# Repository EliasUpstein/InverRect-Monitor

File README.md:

# InverRect-Monitor

**Plataforma Ciberfísica de Simulación, Control HIL y Monitoreo SCADA para Electrónica de Potencia**

---

## 1. Visión y Propósito del Proyecto

**InverRect-Monitor** es una plataforma integral de ingeniería que fusiona la **simulación matemática de alta precisión** con el **control y monitoreo físico en tiempo real** de convertidores estáticos de potencia (rectificadores controlados y no controlados monofásicos y trifásicos, e inversores).

En el estudio y operación de la electrónica de potencia, existe a menudo una desconexión entre:
1. **Los modelos analíticos teóricos:** cálculo de potencias bajo condiciones no senoidales, descomposición en series de Fourier, impacto de armónicas en la red y comportamiento de cargas complejas ($R$, $L$, $C$).
2. **La implementación física de control:** detección precisa del cruce por cero de la red ($50\text{ Hz} / 60\text{ Hz}$), sincronización de microsegundos para el disparo de compuertas (SCR / TRIAC) y aislamiento galvánico de alta tensión.

**InverRect-Monitor** resuelve esta brecha creando un entorno tipo **Hardware-in-the-Loop (HIL) y SCADA**:
* Permite al usuario **analizar, simular y descomponer armónicamente** 12 topologías de convertidores bajo el estándar internacional **IEEE 1459**.
* Permite actuar como **consola SCADA de control remoto**, enviando el ángulo de disparo ($\alpha$) en tiempo real vía **Wi-Fi / UDP** hacia un microcontrolador **ESP32** dedicado al control físico de potencia, garantizando sincronismo estricto e inmunidad a retardos de software.

---

## 2. Arquitectura Global del Sistema Ciberfísico

El sistema opera mediante una división estricta entre la **estación de supervisión de alto nivel (PC)** y el **nodo de control de potencia en tiempo real (ESP32)**:

```
┌─────────────────────────────────────────────────────────────────────────────┐
│                      ESTACIÓN DE SUPERVISIÓN (PC)                           │
│                                                                             │
│   ┌─────────────────────┐   ┌────────────────────────┐   ┌──────────────┐   │
│   │     calculos.py     │◄─►│      interfaz.py       │◄─►│   main.py    │   │
│   │ (NumPy/IEEE 1459/SF)│   │(Tkinter/Matplotlib/UDP)│   │ (Controller) │   │
│   └─────────────────────┘   └───────────┬────────────┘   └──────────────┘   │
└─────────────────────────────────────────┼───────────────────────────────────┘
                                          │ Datagramas UDP ("ALFA:xx.x")
                                          │ Wi-Fi 802.11 (Puerto 8888)
                                          ▼
┌─────────────────────────────────────────────────────────────────────────────┐
│                   NODO DE CONTROL EN TIEMPO REAL (ESP32)                    │
│                                                                             │
│   ┌─────────────────────────────────────┐   ┌───────────────────────────┐   │
│   │               CORE 0                │   │          CORE 1           │   │
│   │   • Tarea FreeRTOS Comunicaciones   │   │   • ISR Cruce por Cero    │   │
│   │   • Servidor UDP & ArduinoOTA       │◄─►│   • Hardware Timer (1 MHz)│   │
│   │   • Sincronización atómica (MUX)    │   │   • Pulso de compuerta    │   │
│   └─────────────────────────────────────┘   └─────────────┬─────────────┘   │
└───────────────────────────────────────────────────────────┼─────────────────┘
                                                            │
                      ┌─────────────────────────────────────┴─────────────┐
                      ▼                                                   ▼
            ┌───────────────────┐                               ┌───────────────────┐
            │  ENTRADA DIGITAL  │                               │  SALIDA DIGITAL   │
            │  GPIO 18 (ZC)     │                               │  GPIO 19 (Gate)   │
            └─────────▲─────────┘                               └─────────┬─────────┘
                      │                                                   │
                      │ Pulso 50 Hz                                       │ Pulso 50 µs
            ┌─────────┴─────────┐                               ┌─────────┴─────────┐
            │ Optoacoplador ZC  │                               │ Driver Opto-TRIAC │
            │      (PC817)      │                               │     (MOC3021)     │
            └─────────▲─────────┘                               └─────────┬─────────┘
                      │                                                   │
     Red Eléctrica ───┴───────────────── Circuito de Potencia ────────────┴──► Carga
     (220V CA / 50 Hz)                   (Tiristores SCR / TRIAC)              (R-L-C)
```

---

## 3. Estructura del Monorepo y Documentación Detallada

El proyecto está organizado de forma modular. Cada subsistema cuenta con su documentación técnica exhaustiva:

```
InverRect-Monitor/
├── pc_software/             # Software de PC: Analizador matemático y panel SCADA
│   ├── calculos.py          # Modelo: Síntesis de ondas, Fourier y cálculo IEEE 1459
│   ├── interfaz.py          # Vista: Interfaz gráfica industrial Tkinter + cliente UDP
│   ├── main.py              # Controlador: Ciclo de vida de la aplicación
│   └── README.md            # 📖 Documentación técnica completa del software de PC
│
├── esp32_firmware/          # Firmware embebido para el microcontrolador ESP32
│   ├── esp32_firmware.ino   # Firmware Dual-Core compatible con Arduino IDE (FreeRTOS, ZCD, ADC, UDP, OTA)
│   └── README.md            # 📖 Documentación técnica de hardware, pines y firmware
│
├── assets/                  # Diagramas y capturas de pantalla
├── .gitignore               # Filtros de Git para entornos Python y compilaciones C++
└── README.md                # 📖 Visión general del proyecto (este archivo)
```

* 👉 **[Documentación del Software de PC (`pc_software/README.md`)](pc_software/README.md):** Contiene la explicación de los cálculos matemáticos (Fourier, impedancias complejas $R$-$X$, formulación IEEE 1459), descripción de las 12 señales simuladas, guía de la interfaz gráfica y configuración del cliente UDP.
* 👉 **[Documentación del Firmware ESP32 (`esp32_firmware/README.md`)](esp32_firmware/README.md):** Contiene el diagrama de conexionado eléctrico, pinout (GPIO 18 y 19), configuración de FreeRTOS, actualización inalámbrica vía ArduinoOTA y sincronización atómica con spinlocks.

---

## 4. Características Principales

### 🔬 Análisis Matemático y Procesamiento de Señales
* **Correlación Trigonométrica de Fourier (sin FFT):** Cálculo exacto de coeficientes ($a_n, b_n$) mediante integración numérica en el dominio temporal discreto. Evita problemas de *picket-fence* y dispersión espectral (*spectral leakage*) propios de la FFT en señales no periódicas o truncadas.
* **Norma IEEE 1459:** Computa potencia activa ($P$), aparente ($S$), reactiva fundamental ($Q$), distorsión armónica ($D$), factor de potencia ($FP = P/S$) y distorsión armónica total de tensión y corriente ($\text{THD}_V, \text{THD}_I$).
* **Modelado de Impedancias Complejas:** Respuesta dinámica de corriente considerando armónica fundamental y armónicas superiores ($X_n = nX$ para cargas inductivas y $X_n = X/n$ para capacitivas).
* **Biblioteca de 12 Topologías:** Senoidal pura, cuadrada, cuasi-cuadrada, rectificadores monofásicos y trifásicos (media onda y onda completa, controlados y no controlados) y simulación de entrada analógica ADC con ruido gaussiano.

### 🖥️ Interfaz Gráfica SCADA de Alta Legibilidad
* **Diseño Industrial:** Optimizado para pantallas industriales y monitores con escalado DPI (hasta 1080p con 125% DPI scaling).
* **Visualización en Dos Subplots:**
  * Dominio del tiempo: tensión y corriente superpuestas en 2 ciclos con marcación del ángulo $\alpha$.
  * Dominio de la frecuencia: espectro de barras lado a lado de armónicas RMS de tensión y corriente.
* **Cursores Interactivos:** Inspección de valores puntuales al hacer clic sobre cualquier punto de las curvas.
* **Modo en Tiempo Real:** Bucle de simulación y refresco continuo configurable en segundos.

### ⚡ Control de Hardware Físico en Tiempo Real
* **Microsegundos de Precisión:** El ESP32 ejecuta la sincronización de cruce por cero y el temporizador de hardware en el Core 1 con código en `IRAM`, asegurando un disparo libre de jitter. Incorpora un filtro de ventana de supresión de $7000\,\mu\text{s}$ contra transitorios y rebotes en la red de 50 Hz.
* **Enlace Inalámbrico Bidireccional con Handshake (ACK/NACK):** El operador configura la IP en la PC y despacha el comando `"ALFA:xx.x"`. La aplicación verifica activamente la conexión aguardando el paquete de confirmación `"ACK:ALFA:xx.x"` emitido por el ESP32, alertando con precisión si el microcontrolador está apagado o la IP es inalcanzable.
* **Protección de Seguridad Industrial y Monotonicidad:** Compensación continua de retardo de optoacoplador que previene saltos bruscos en bajas conducciones, y validación automática en la interfaz que restringe el ángulo estrictamente al rango seguro $0.0^\circ \le \alpha \le 180.0^\circ$.
* **Flasheo Inalámbrico (OTA):** Soporte para reprogramar el firmware del ESP32 a distancia mientras se encuentra instalado en el banco de pruebas.

---

## 5. Modos de Operación

El sistema puede utilizarse en tres modalidades operativas:

1. **Modo Simulación Pura (Educativo / Diseño):**
   * Se selecciona cualquiera de las topologías de convertidor (índices 0 a 10).
   * Se ajusta la amplitud de tensión, el ángulo de disparo teórico $\alpha$ y los valores de $R$ y $X$.
   * La aplicación reconstruye las ondas analíticas y calcula inmediatamente todos los parámetros de calidad de energía y el espectro armónico.
2. **Modo Hardware-in-the-Loop (HIL) y Control Remoto:**
   * La aplicación de PC se conecta al ESP32 ingresando su dirección IP en la sección de control de hardware.
   * Al modificar $\alpha$ y presionar **"Enviar Ángulo (α) al Hardware"**, el ESP32 actualiza instantáneamente el retardo de compuerta en el circuito de tiristores real.
   * Permite contrastar la respuesta teórica calculada en la PC contra las mediciones en osciloscopio tomadas sobre el convertidor físico.
3. **Modo Instrumentación / Telemetría ADC:**
   * Seleccionando la señal `11. Muestras ADC (Simuladas)`, el sistema evalúa señales analógicas adquiridas con componentes estocásticos de ruido.
   * Permite continuar despachando órdenes de hardware al ESP32 manteniendo independiente el análisis de la señal capturada.

---

## 6. Puesta en Marcha Rápida (Quickstart)

### Paso 1: Clonar el Repositorio
```bash
git clone https://github.com/EliasUpstein/InverRect-Monitor.git
cd InverRect-Monitor
```

### Paso 2: Configurar el Entorno Python
```bash
# Crear entorno virtual
python -m venv venv

# Activar entorno virtual
# En Windows:
venv\Scripts\activate
# En Linux/macOS:
source venv/bin/activate

# Instalar dependencias
pip install numpy matplotlib
```

### Paso 3: Ejecutar la Interfaz de PC
```bash
python pc_software/main.py
```

### Paso 4 (Opcional): Cargar el Firmware al ESP32
1. Abrir la carpeta `esp32_firmware/` en PlatformIO o Arduino IDE.
2. Configurar `WIFI_SSID` y `WIFI_PASSWORD` en `esp32_firmware/main.cpp`.
3. Flashear el microcontrolador y observar la IP en el Monitor Serie (115200 bps).
4. Configurar la IP en `pc_software/interfaz.py` para habilitar el control inalámbrico.

---

## 7. Referencias Normativas y Bibliográficas
* **IEEE Std 1459-2010:** *IEEE Standard Definitions for the Measurement of Electric Power Quantities Under Sinusoidal, Nonsinusoidal, Balanced, or Unbalanced Conditions*.
* **Mohan, Undeland, Robbins:** *Power Electronics: Converters, Applications, and Design*, John Wiley & Sons.
* **Rashid, Muhammad H.:** *Power Electronics Handbook*, Academic Press.
* **Espressif Systems:** *ESP32 Technical Reference Manual & FreeRTOS Architecture*.

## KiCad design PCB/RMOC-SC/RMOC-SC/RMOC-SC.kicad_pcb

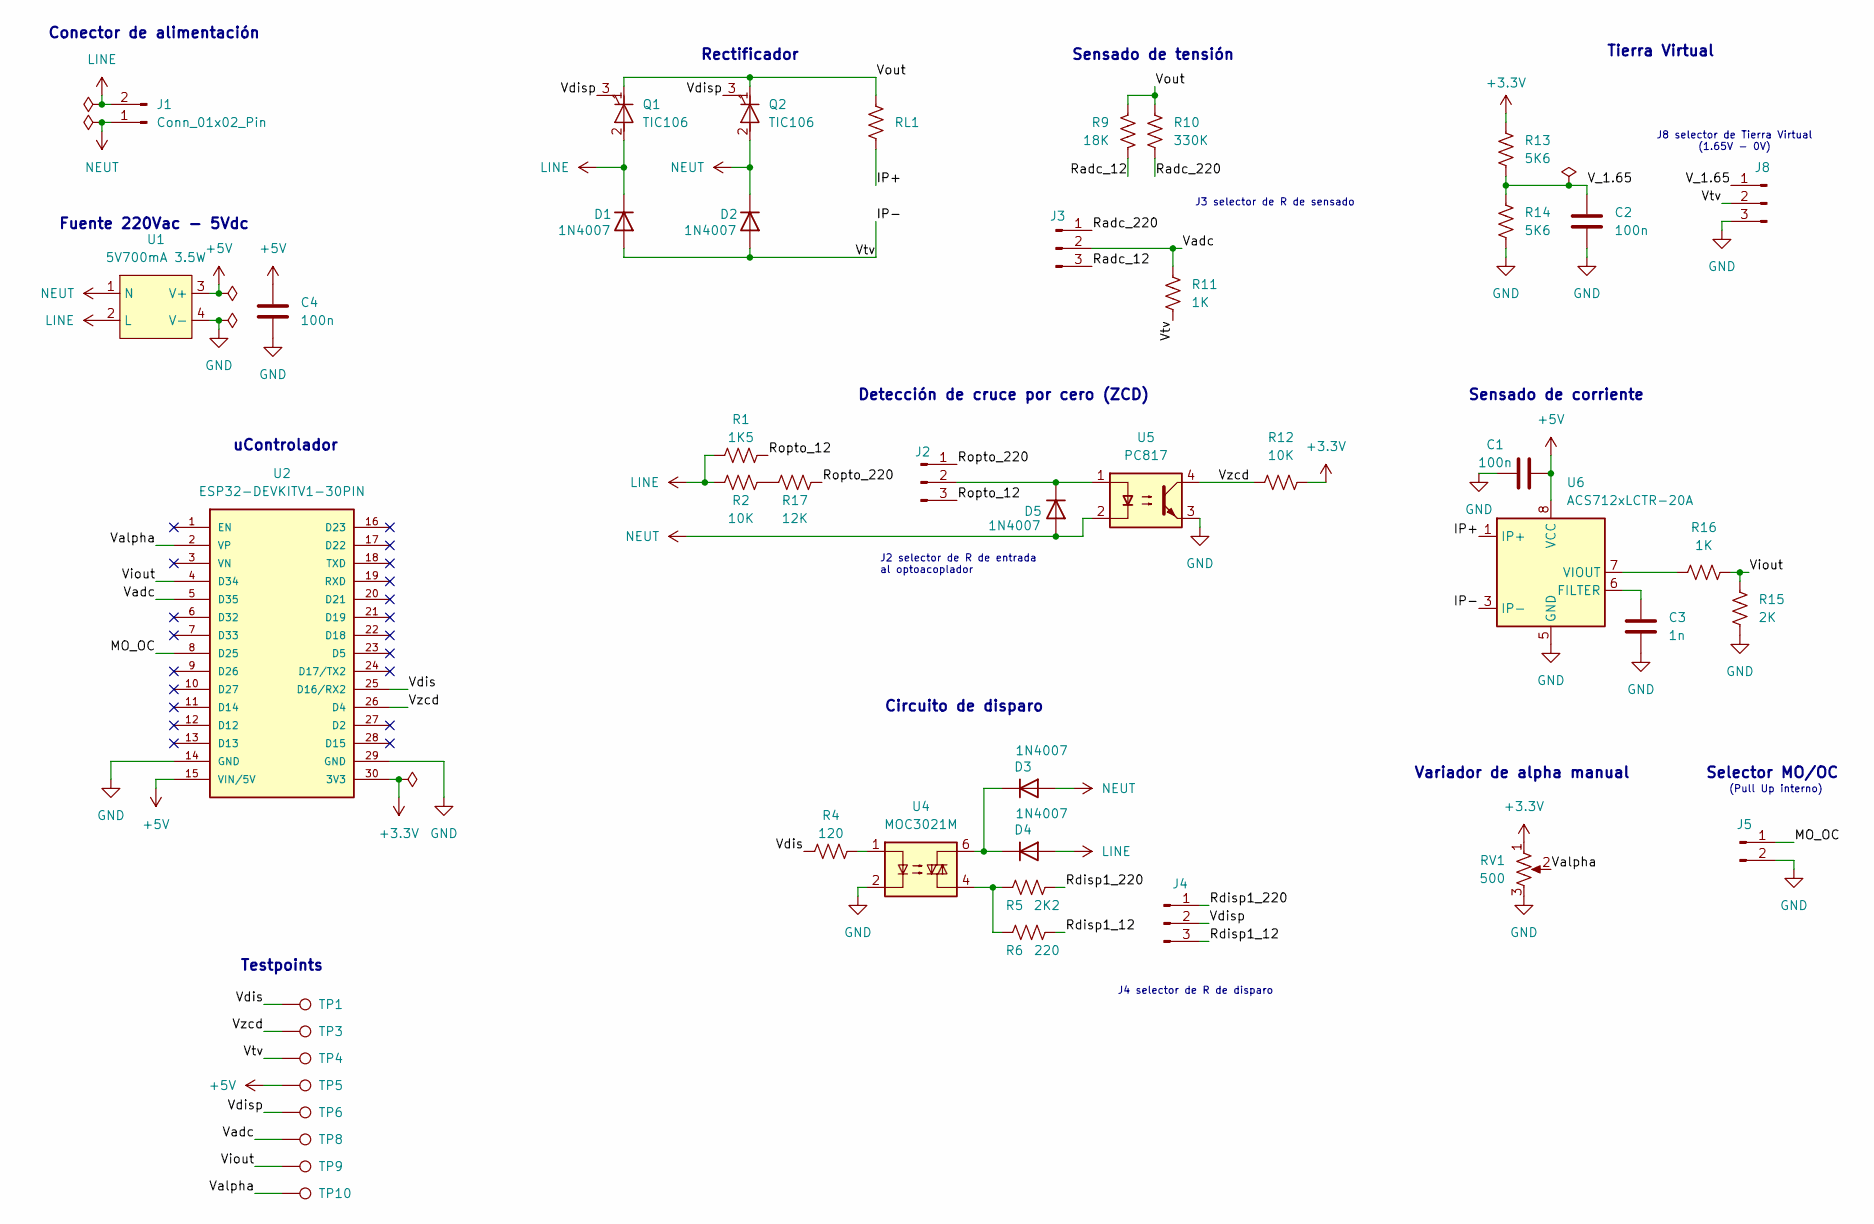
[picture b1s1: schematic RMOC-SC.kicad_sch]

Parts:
C1, C2, C4: 100n; C_Disc_D5.0mm_W2.5mm_P5.00mm
C3: 1n; C_Disc_D5.0mm_W2.5mm_P5.00mm
D1, D2, D3, D4, D5: 1N4007; D_DO-41_SOD81_P10.16mm_Horizontal
J1: Conn_01x02_Pin; Conn_220_tipo8
J2, J3, J4, J8: Conn_01x03_Pin; PinHeader_1x03_P2.54mm_Vertical
J5: Conn_01x02_Pin; PinHeader_1x02_P2.54mm_Vertical
Q1, Q2: TIC106; TO-220-3_Vertical
R1: 1K5; R_Axial_DIN0309_L9.0mm_D3.2mm_P12.70mm_Horizontal
R2: 10K; R_Axial_DIN0614_L14.3mm_D5.7mm_P20.32mm_Horizontal
R4: 120; R_Axial_DIN0309_L9.0mm_D3.2mm_P12.70mm_Horizontal
R5: 2K2; R_Axial_DIN0309_L9.0mm_D3.2mm_P12.70mm_Horizontal
R6: 220; R_Axial_DIN0309_L9.0mm_D3.2mm_P12.70mm_Horizontal
R9: 18K; R_Axial_DIN0309_L9.0mm_D3.2mm_P12.70mm_Horizontal
R10: 330K; R_Axial_DIN0309_L9.0mm_D3.2mm_P12.70mm_Horizontal
R11, R16: 1K; R_Axial_DIN0309_L9.0mm_D3.2mm_P12.70mm_Horizontal
R12: 10K; R_Axial_DIN0309_L9.0mm_D3.2mm_P12.70mm_Horizontal
R13, R14: 5K6; R_Axial_DIN0309_L9.0mm_D3.2mm_P12.70mm_Horizontal
R15: 2K; R_Axial_DIN0309_L9.0mm_D3.2mm_P12.70mm_Horizontal
R17: 12K; R_Axial_DIN0614_L14.3mm_D5.7mm_P20.32mm_Horizontal
RL1: R_US; Altech_AK100_1x02_P5.00mm
RV1: 500; Potentiometer_Piher_PC-16_Single_Horizontal
TP1, TP3, TP4, TP5, TP6, TP8, TP9, TP10: TestPoint; PinHeader_1x01_P2.54mm_Vertical
U1: 5V700mA 3.5W; WX-DC12003
U2: ESP32-DEVKITV1-30PIN; ESP32-DEVKIT-30PIN; PARTREV V4
U4: MOC3021M; DIP-6_W7.62mm_LongPads
U5: PC817; DIP-4_W7.62mm
U6: ACS712xLCTR-20A; SOIC-8_3.9x4.9mm_P1.27mm

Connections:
+3.3V: R12.2, R13.1, RV1.1, U2.30 (3V3)
+5V: C1.2, C4.1, TP5.1 (1_1), U1.3 (V+), U2.15 (VIN/5V), U6.8 (VCC)
/IP+: RL1.2, U6.1 (IP+), U6.2 (IP+)
/IP-: D1.2 (A), D2.2 (A), J8.2, R11.2, TP4.1 (1_1), U6.3 (IP-), U6.4 (IP-)
/MO_OC: J5.1, U2.8 (D25)
/Radc_12: J3.3, R9.2
/Radc_220: J3.1, R10.2
/Rdisp1_12: J4.3, R6.2
/Rdisp1_220: J4.1, R5.2
/Ropto_12: J2.3, R1.2
/Ropto_220: J2.1, R17.2
/V_1.65: C2.1, J8.1, R13.2, R14.1
/Vadc: J3.2, R11.1, TP8.1 (1_1), U2.5 (D35)
/Valpha: RV1.2, TP10.1 (1_1), U2.2 (VP)
/Vdis: R4.1, TP1.1 (1_1), U2.25 (D16/RX2)
/Vdisp: J4.2, Q1.3 (G), Q2.3 (G), TP6.1 (1_1)
/Viout: R15.1, R16.2, TP9.1 (1_1), U2.4 (D34)
/Vout: Q1.1 (K), Q2.1 (K), R9.1, R10.1, RL1.1
/Vzcd: R12.1, TP3.1 (1_1), U2.26 (D4), U5.4
GND: C1.1, C2.2, C3.2, C4.2, J5.2, J8.3, R14.2, R15.2, RV1.3, U1.4 (V-), U2.14 (GND), U2.29 (GND), U4.2, U5.3, U6.5 (GND)
LINE: D1.1 (K), D4.2 (A), J1.2, Q1.2 (A), R1.1, R2.1, U1.2 (L)
NEUT: D2.1 (K), D3.2 (A), D5.2 (A), J1.1, Q2.2 (A), U1.1 (N), U5.2
unnamed: D3.1 (K), D4.1 (K), U4.6
unnamed: D5.1 (K), J2.2, U5.1
unnamed: R4.2, U4.1
unnamed: R5.1, R6.1, U4.4
unnamed: R2.2, R17.1
unnamed: C3.1, U6.6 (FILTER)
unnamed: R16.1, U6.7 (VIOUT)

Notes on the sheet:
Rectificador
Detección de cruce por cero (ZCD)
Sensado de corriente
Variador de alpha manual
J8 selector de Tierra Virtual (1.65V - 0V)
Testpoints
Fuente 220Vac - 5Vdc
J2 selector de R de entrada al optoacoplador
Selector MO/OC
uControlador
Circuito de disparo
(Pull Up interno)
J4 selector de R de disparo
Sensado de tensión
J3 selector de R de sensado
Tierra Virtual
Conector de alimentación

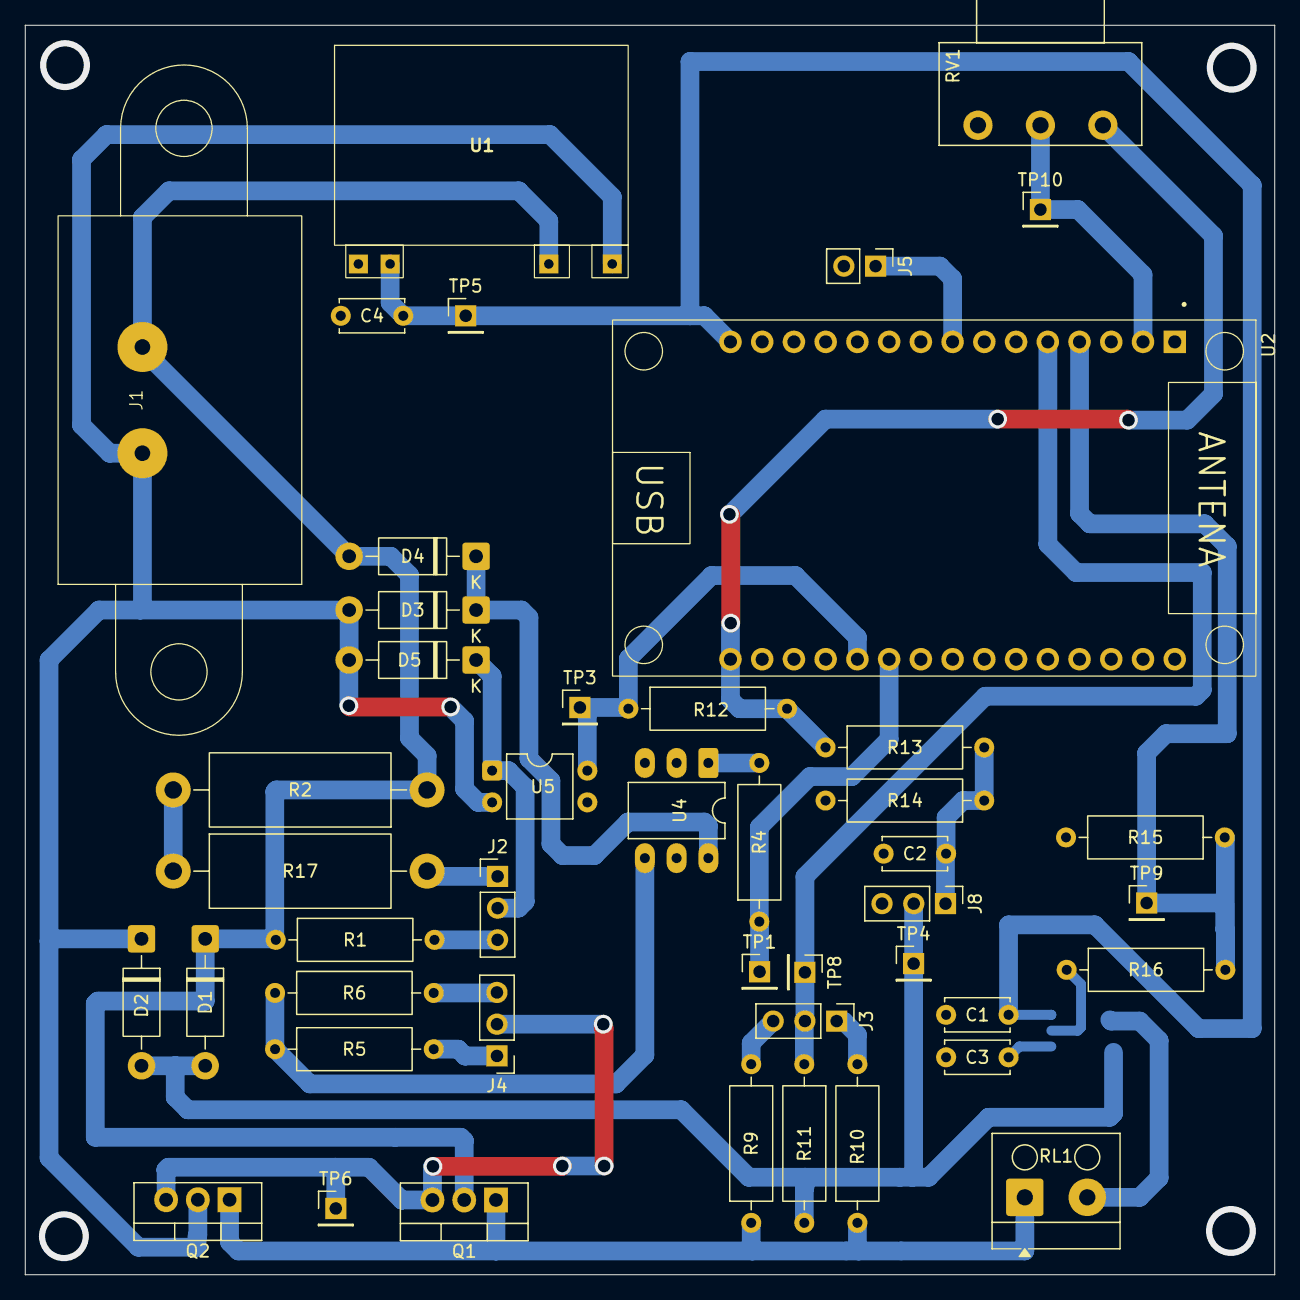
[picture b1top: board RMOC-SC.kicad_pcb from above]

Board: 2 copper layers, 100.0 x 100.0 mm, 46 parts (1 on the bottom side), 29 nets.
